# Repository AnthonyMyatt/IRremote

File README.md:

# IRremote for Beaglebone

## What is it?

**IRremote for Beaglebone** is a cape and relevant software that work together to make controlling things like television sets, DVD players, or any other IR controlled device with your Beaglebone or Beaglebone-Black.

### The Cape
The IR Cape consists of three LED outputs that can be connected to IR extender cables such as this one

<br/>
and can then be used to control up to three devices (or more, by using one IR cable for multiple devices if they don't share IR codes).

### The Node.JS Module
The module for node.js is where the magic happens. With only three lines of javascript you can turn your TV on.

```javascript
var IR = require("./build/Release/IRremote.node");
var IRsend = new IR.IRsend();
IRsend.sendSony(0xa90, 12, IR.SEND_PIN_1, function() {});
```

## Recognition
#### IRremote for Arduino (Ken Shirriff)
The Node.JS module is based off of Ken Shirriff's IRremote library for the Arduino. You can find information on Ken's library on his [blog](http://www.righto.com/2009/08/multi-protocol-infrared-remote-library.html).

***Please note***: Although the function names are the same as Ken's library, the arguments that the functions take are different and the internal workings of the functions are different due to the differences in hardware.

## License

<br />This work is licensed under a <a rel="license" href="http://creativecommons.org/licenses/by-nc-sa/3.0/deed.en_US">Creative Commons Attribution-NonCommercial-ShareAlike 3.0 Unported License</a>.

A copy of the license can be found within the LICENSE file that should be in the same directory as this README file. If the license file is not included, you can find a copy of the license on the Creative Commons website.

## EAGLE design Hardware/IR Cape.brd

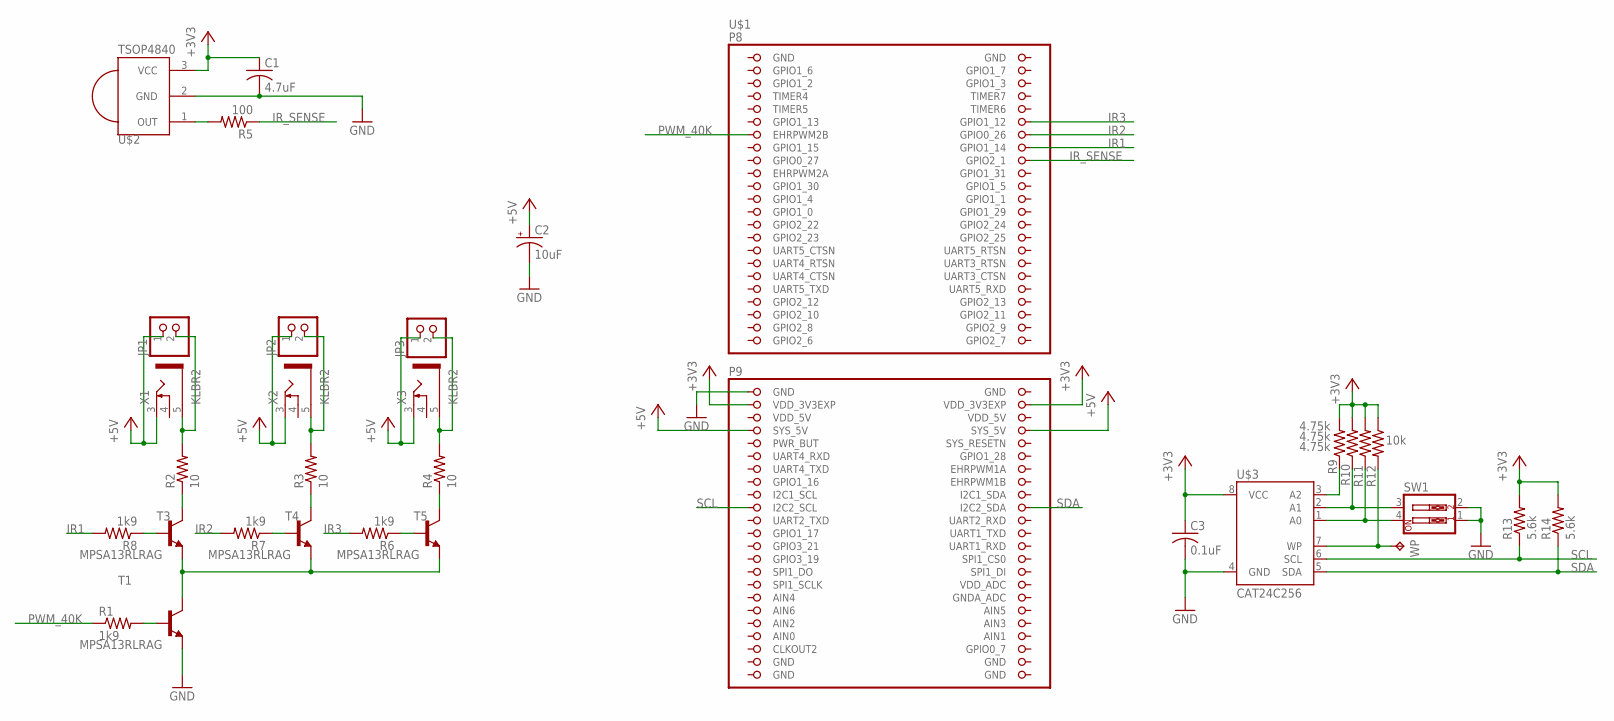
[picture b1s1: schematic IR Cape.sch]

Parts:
C1: 4.7uF; C025-024X044
C2: 10uF; E2-5
C3: 0.1uF; C025-024X044
JP1, JP2, JP3: PINHD-1X2; 1X02
R1, R6, R7, R8: 1k9; 0207/10
R2, R3, R4: 10; 0207/10
R5: 100; 0207/10
R9, R10, R11: 4.75k; 0207/10
R12: 10k; 0207/10
R13, R14: 5.6k; 0207/10
SW1: SW_DIP-2; EDG-02
T1, T3, T4, T5: MPSA13RLRAG; TO92-EBC
U$1: BEAGLEBONE_OUTLINE; BEAGLEBONE_SHIELD
U$2: TSOP4840; PNA460XM
U$3: CAT24C256
WP: TPB1,27; B1,27
X1, X2, X3: KLBR2

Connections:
+3V3: C1.1, C3.1, R9.2, R10.2, R11.2, R12.1, R13.2, R14.2, U$1.49 (VDD_3V3EXP), U$1.50 (VDD_3V3EXP), U$2.3 (VCC), U$3.8 (VCC)
+5V: C2.+, JP1.1, JP2.1, JP3.1, U$1.53 (SYS_5V), U$1.54 (SYS_5V), X1.3, X2.3, X3.3
AIN0: U$1.85 (AIN0)
GND: C1.2, C2.-, C3.2, SW1.1, SW1.2, T1.E, U$1.1 (GND), U$1.2 (GND), U$1.47 (GND), U$1.48 (GND), U$1.89 (GND), U$1.90 (GND), U$1.91 (GND), U$1.92 (GND), U$2.2 (GND), U$3.4 (GND)
IR1: R8.2, U$1.16 (GPIO1_14)
IR2: R7.2, U$1.14 (GPIO0_26)
IR3: R6.2, U$1.12 (GPIO1_12)
IR_SENSE: R5.1, U$1.18 (GPIO2_1)
unnamed: JP1.2, R2.2, X1.5
unnamed: T1.C, T3.E, T4.E, T5.E
unnamed: R1.2, T1.B
unnamed: R4.1, T5.C
unnamed: JP3.2, R4.2, X3.5
unnamed: R3.1, T4.C
unnamed: R2.1, T3.C
unnamed: JP2.2, R3.2, X2.5
unnamed: R5.2, U$2.1 (OUT)
unnamed: R11.1, SW1.4, U$3.1 (A0)
unnamed: R8.1, T3.B
unnamed: R7.1, T4.B
unnamed: R6.1, T5.B
unnamed: R10.1, SW1.3, U$3.2 (A1)
unnamed: R12.2, U$3.7 (WP), WP.TP
unnamed: R9.1, U$3.3 (A2)
PWM_40K: R1.1, U$1.13 (EHRPWM2B)
SCL: R13.1, U$1.65 (I2C2_SCL), U$3.6 (SCL)
SDA: R14.1, U$1.66 (I2C2_SDA), U$3.5 (SDA)
VDD_5V: U$1.51 (VDD_5V), U$1.52 (VDD_5V)

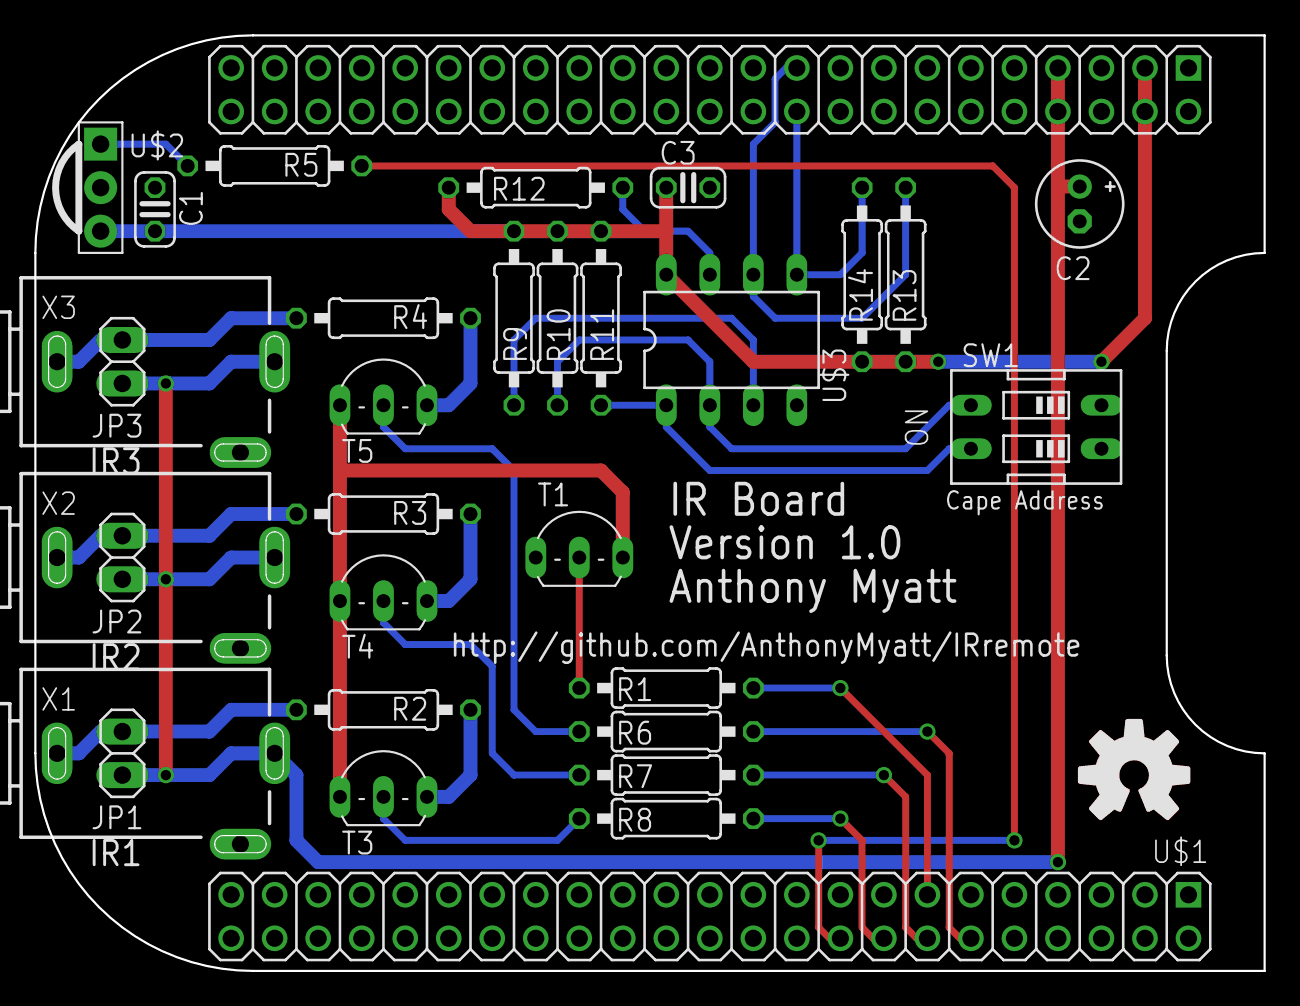
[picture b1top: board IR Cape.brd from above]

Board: 2 copper layers, 71.8 x 54.6 mm, 32 parts (1 on the bottom side), 27 nets.

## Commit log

2000-01-01 Got the basics for test4 working.
2013-07-31 Removed Vim Cahce Files (tilda files, swap files, etc)
2013-07-31 Added test2
2013-08-01 Updated License
2013-08-01 Added support for RAW IR commands
2013-08-01 Minor changes
2013-08-01 Added Test3
2013-08-01 Fixed Raw, changed test 2
2013-08-02 Migrated from SimpleGPIO to Beagle_GPIO in an attempt to improve digitalWrite speeds.
2013-08-12 Modified Mark and Space functions to remove 100ns from the time (I'm assuming this is due to the added delay to execute the GPIO function.
2013-08-23 Added new test file (test4.js)
2013-08-25 Forgot to add testDevices file for test4
2013-08-25 Moved software into a sub-folder and added the Eagle schematic and PCB files
2013-08-25 Fixed resistor values in schematic
2013-08-28 Added IRlib submodule
2013-08-28 Moved Node.JS Module files into 'Node Module'
2013-08-28 Moved README and LICENSE back to where they should be
2013-08-29 Changed Readme to show correct license
2013-08-29 Added License File
2013-08-29 Removed Hardware Files
